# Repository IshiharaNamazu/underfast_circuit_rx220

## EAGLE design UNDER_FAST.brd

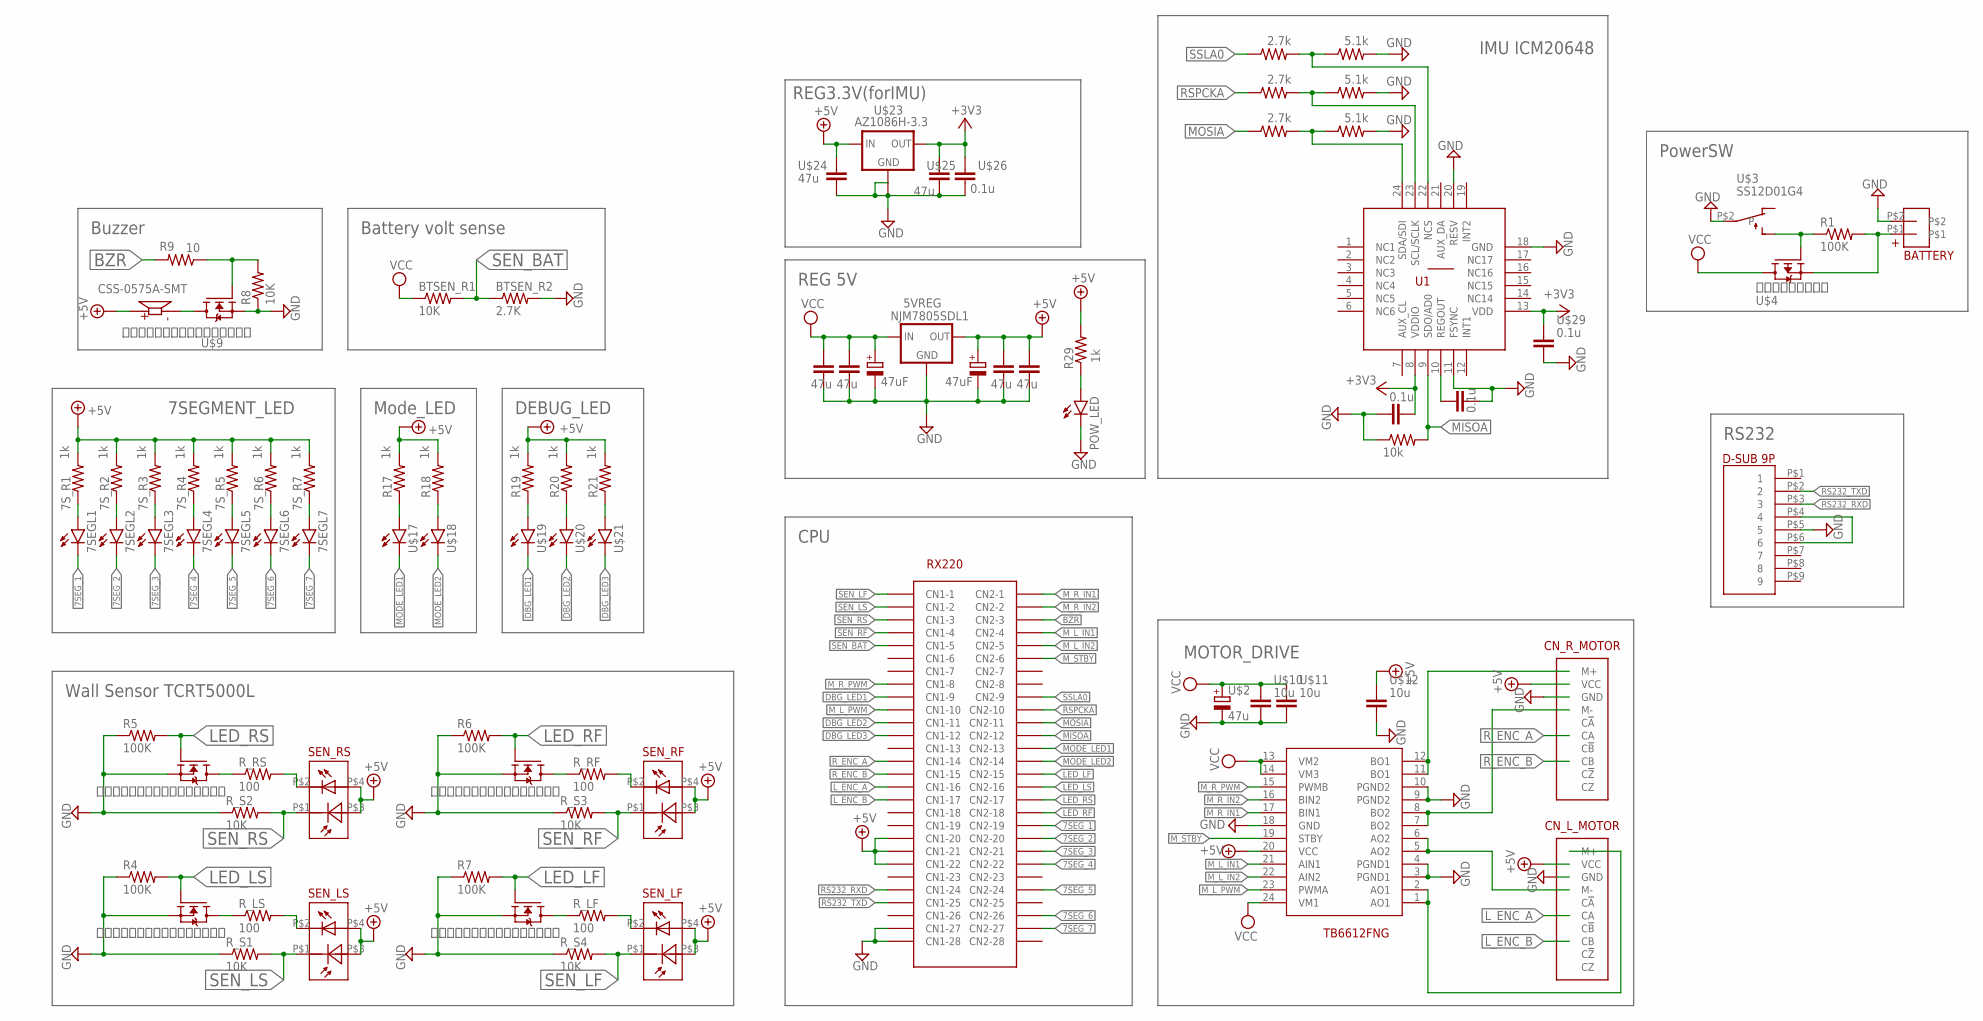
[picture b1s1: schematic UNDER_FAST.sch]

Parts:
5VREG: NJM7805SDL1; TO252
7SEGL1, 7SEGL2, 7SEGL3, 7SEGL4, 7SEGL5, 7SEGL6, 7SEGL7: LED1608
7S_R1, 7S_R2, 7S_R3, 7S_R4, 7S_R5, 7S_R6, 7S_R7: 1k; RESC1005X40N
BATTERY: DF3A_2P_2DSA_CONNECTOR
BTSEN_R1: 10K; RESC1005X40N
BTSEN_R2: 2.7K; RESC1005X40N
C1, C2, C3, C4: 47u; CAPC3225X270N
CLK_R1: 2.7k; RESC1005X40N
CLK_R2: 5.1k; RESC1005X40N
CN_L_MOTOR: CN_MOTOR
CN_R_MOTOR: CN_MOTOR
EC1, EC2: 47uF; CAPAE660X800N
LS1: CSS-0575A-SMT; CUI_CSS-0575A-SMT
MISO_R: 10k; RESC1005X40N
MOSI_R1: 2.7k; RESC1005X40N
MOSI_R2: 5.1k; RESC1005X40N
NCS_R1: 2.7k; RESC1005X40N
NCS_R2: 5.1k; RESC1005X40N
POW_LED: LED1608
R1, R4, R5, R6, R7: 100K; RESC1005X40N
R8: 10K; RESC1005X40N
R9: 10; RESC1005X40N
R17, R18, R19, R20, R21, R29: 1k; RESC1005X40N
R_LF: 100; RESC1005X40N
R_LS: 100; RESC1005X40N
R_RF: 100; RESC1005X40N
R_RS: 100; RESC1005X40N
R_S1, R_S2, R_S3, R_S4: 10K; RESC1005X40N
SEN_LF: TCRT5000L; TCRT5000L_PHOTO
SEN_LS: TCRT5000L; TCRT5000L_PHOTO
SEN_RF: TCRT5000L; TCRT5000L_PHOTO
SEN_RS: TCRT5000L; TCRT5000L_PHOTO
TB6612FNG: TB6612FNG; SOP65P760X160-24N
U1: ICM-20648; QFN40P300X300X95-24N
U$1: RX220_BOARD
U$2: 47u; CAPAE660X800N
U$3: SS12D01G4
U$4: ＩＲＬＭＬ６４０２; SOT23
U$5, U$6, U$7, U$8, U$9: ＩＲＬＭＬ６３４４ＴＲＰＢＦＴＲ; SOT23
U$10, U$11, U$12: 10u; CAPC3216X180N
U$13: D-SUB
U$17, U$18, U$19, U$20, U$21: LED1608
U$23: AZ1086H-3.3; SOT223
U$24, U$25: 47u; CAPC3225X270N
U$26, U$27, U$28, U$29: 0.1u; CAPC1005X55N

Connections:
7SEG_1: 7SEGL1.P$2 (C), U$1.P$47 (CN2-19)
7SEG_2: 7SEGL2.P$2 (C), U$1.P$48 (CN2-20)
7SEG_3: 7SEGL3.P$2 (C), U$1.P$49 (CN2-21)
7SEG_4: 7SEGL4.P$2 (C), U$1.P$50 (CN2-22)
7SEG_5: 7SEGL5.P$2 (C), U$1.P$52 (CN2-24)
7SEG_6: 7SEGL6.P$2 (C), U$1.P$54 (CN2-26)
7SEG_7: 7SEGL7.P$2 (C), U$1.P$55 (CN2-27)
+3V3: U1.8 (VDDIO), U1.13 (VDD), U$23.2 (OUT), U$25.1, U$26.1, U$28.1, U$29.1
+5V: 5VREG.2 (OUT), 7S_R1.2, 7S_R2.2, 7S_R3.2, 7S_R4.2, 7S_R5.2, 7S_R6.2, 7S_R7.2, C3.1, C4.1, CN_L_MOTOR.P$2 (VCC), CN_R_MOTOR.P$2 (VCC), EC2.1 (+), LS1.1, R17.2, R18.2, R19.2, R20.2, R21.2, R29.2, SEN_LF.P$3 (DIODE+), SEN_LF.P$4 (LED+), SEN_LS.P$3 (DIODE+), SEN_LS.P$4 (LED+), SEN_RF.P$3 (DIODE+), SEN_RF.P$4 (LED+), SEN_RS.P$3 (DIODE+), SEN_RS.P$4 (LED+), TB6612FNG.20 (VCC), U$1.P$20 (CN1-20), U$1.P$21 (CN1-21), U$1.P$22 (CN1-22), U$12.1, U$23.3 (IN), U$24.1
BZR: R9.2, U$1.P$31 (CN2-3)
DBG_LED1: U$1.P$9 (CN1-9), U$19.P$2 (C)
DBG_LED2: U$1.P$11 (CN1-11), U$20.P$2 (C)
DBG_LED3: U$1.P$12 (CN1-12), U$21.P$2 (C)
GND: 5VREG.3 (GND), BATTERY.P$2, BTSEN_R2.2, C1.2, C2.2, C3.2, C4.2, CLK_R2.2, CN_L_MOTOR.P$3 (GND), CN_R_MOTOR.P$3 (GND), EC1.2 (-), EC2.2 (-), MISO_R.1, MOSI_R2.2, NCS_R2.2, POW_LED.P$2 (C), R4.1, R5.1, R6.1, R7.1, R8.1, R_S1.1, R_S2.1, R_S3.1, R_S4.1, TB6612FNG.3 (PGND1), TB6612FNG.4 (PGND1), TB6612FNG.9 (PGND2), TB6612FNG.10 (PGND2), TB6612FNG.18 (GND), U1.11 (FSYNC), U1.18 (GND), U1.20 (RESV), U$1.P$27 (CN1-27), U$1.P$28 (CN1-28), U$2.2 (-), U$3.P$2, U$5.2 (S), U$6.2 (S), U$7.2 (S), U$8.2 (S), U$9.2 (S), U$10.2, U$11.2, U$12.2, U$13.P$5 (5), U$23.1 (GND), U$23.4 (GND1), U$24.2, U$25.2, U$26.2, U$27.2, U$28.2, U$29.2
LED_LF: R7.2, U$1.P$43 (CN2-15), U$8.1 (G)
LED_LS: R4.2, U$1.P$44 (CN2-16), U$6.1 (G)
LED_RF: R6.2, U$1.P$46 (CN2-18), U$7.1 (G)
LED_RS: R5.2, U$1.P$45 (CN2-17), U$5.1 (G)
L_ENC_A: CN_L_MOTOR.P$6 (CA), U$1.P$16 (CN1-16)
L_ENC_B: CN_L_MOTOR.P$8 (CB), U$1.P$17 (CN1-17)
MISOA: MISO_R.2, U1.9 (SDO/AD0), U$1.P$40 (CN2-12)
MODE_LED1: U$1.P$41 (CN2-13), U$17.P$2 (C)
MODE_LED2: U$1.P$42 (CN2-14), U$18.P$2 (C)
MOSIA: MOSI_R1.1, U$1.P$39 (CN2-11)
M_L_IN1: TB6612FNG.21 (AIN1), U$1.P$32 (CN2-4)
M_L_IN2: TB6612FNG.22 (AIN2), U$1.P$33 (CN2-5)
M_L_PWM: TB6612FNG.23 (PWMA), U$1.P$10 (CN1-10)
M_R_IN1: TB6612FNG.17 (BIN1), U$1.P$29 (CN2-1)
M_R_IN2: TB6612FNG.16 (BIN2), U$1.P$30 (CN2-2)
M_R_PWM: TB6612FNG.15 (PWMB), U$1.P$8 (CN1-8)
M_STBY: TB6612FNG.19 (STBY), U$1.P$34 (CN2-6)
unnamed: BATTERY.P$1, R1.2, U$4.2 (S)
unnamed: R1.1, U$3.P$3 (ON), U$4.1 (G)
unnamed: R_LS.2, SEN_LS.P$2 (LED-)
unnamed: R_LS.1, U$6.3 (D)
unnamed: R_RS.1, U$5.3 (D)
unnamed: R_RS.2, SEN_RS.P$2 (LED-)
unnamed: R_RF.1, U$7.3 (D)
unnamed: R_RF.2, SEN_RF.P$2 (LED-)
unnamed: R_LF.1, U$8.3 (D)
unnamed: R_LF.2, SEN_LF.P$2 (LED-)
unnamed: CN_R_MOTOR.P$1 (M+), TB6612FNG.11 (BO1), TB6612FNG.12 (BO1)
unnamed: R8.2, R9.1, U$9.1 (G)
unnamed: CN_R_MOTOR.P$4 (M-), TB6612FNG.7 (BO2), TB6612FNG.8 (BO2)
unnamed: CN_L_MOTOR.P$4 (M-), TB6612FNG.5 (AO2), TB6612FNG.6 (AO2)
unnamed: LS1.2 (N), U$9.3 (D)
unnamed: CN_L_MOTOR.P$1 (M+), TB6612FNG.1 (AO1), TB6612FNG.2 (AO1)
unnamed: 7SEGL1.P$1 (A), 7S_R1.1
unnamed: 7SEGL2.P$1 (A), 7S_R2.1
unnamed: 7SEGL3.P$1 (A), 7S_R3.1
unnamed: 7SEGL4.P$1 (A), 7S_R4.1
unnamed: 7SEGL5.P$1 (A), 7S_R5.1
unnamed: 7SEGL6.P$1 (A), 7S_R6.1
unnamed: 7SEGL7.P$1 (A), 7S_R7.1
unnamed: R17.1, U$17.P$1 (A)
unnamed: R18.1, U$18.P$1 (A)
unnamed: R19.1, U$19.P$1 (A)
unnamed: R20.1, U$20.P$1 (A)
unnamed: R21.1, U$21.P$1 (A)
unnamed: U$13.P$4 (4), U$13.P$6 (6)
unnamed: MOSI_R1.2, MOSI_R2.1, U1.24 (SDA/SDI)
unnamed: CLK_R1.2, CLK_R2.1, U1.23 (SCL/SCLK)
unnamed: U1.10 (REGOUT), U$27.1
unnamed: NCS_R1.2, NCS_R2.1, U1.22 (NCS)
unnamed: POW_LED.P$1 (A), R29.1
RS232_RXD: U$1.P$24 (CN1-24), U$13.P$3 (3)
RS232_TXD: U$1.P$25 (CN1-25), U$13.P$2 (2)
RSPCKA: CLK_R1.1, U$1.P$38 (CN2-10)
R_ENC_A: CN_R_MOTOR.P$6 (CA), U$1.P$14 (CN1-14)
R_ENC_B: CN_R_MOTOR.P$8 (CB), U$1.P$15 (CN1-15)
SEN_BAT: BTSEN_R1.2, BTSEN_R2.1, U$1.P$5 (CN1-5)
SEN_LF: R_S4.2, SEN_LF.P$1 (DIODE-), U$1.P$1 (CN1-1)
SEN_LS: R_S1.2, SEN_LS.P$1 (DIODE-), U$1.P$2 (CN1-2)
SEN_RF: R_S3.2, SEN_RF.P$1 (DIODE-), U$1.P$4 (CN1-4)
SEN_RS: R_S2.2, SEN_RS.P$1 (DIODE-), U$1.P$3 (CN1-3)
SSLA0: NCS_R1.1, U$1.P$37 (CN2-9)
VCC: 5VREG.1 (IN), BTSEN_R1.1, C1.1, C2.1, EC1.1 (+), TB6612FNG.13 (VM2), TB6612FNG.14 (VM3), TB6612FNG.24 (VM1), U$2.1 (+), U$4.3 (D), U$10.1, U$11.1

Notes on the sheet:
PowerSW
REG 5V
Battery volt sense
Wall Sensor TCRT5000L
MOTOR_DRIVE
Buzzer
7SEGMENT_LED
Mode_LED
DEBUG_LED
RS232
REG3.3V(forIMU)
IMU ICM20648
CPU

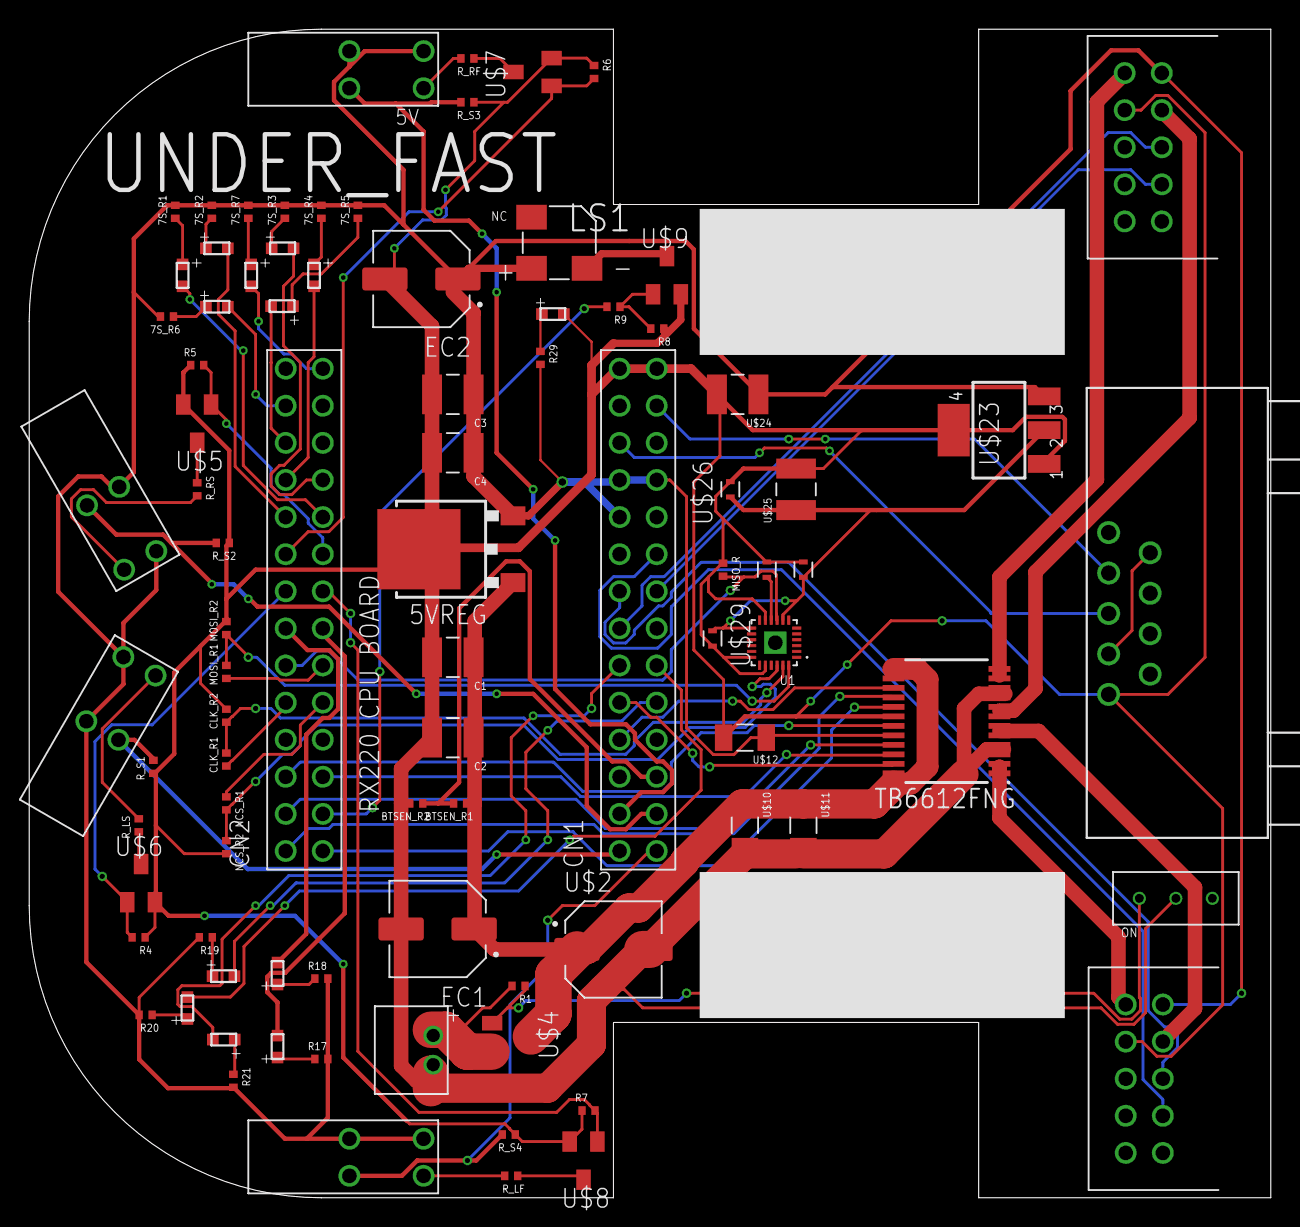
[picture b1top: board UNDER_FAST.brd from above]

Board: 2 copper layers, 85.0 x 80.0 mm, 87 parts (0 on the bottom side), 77 nets.

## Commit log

2021-06-30 最初のコミット
